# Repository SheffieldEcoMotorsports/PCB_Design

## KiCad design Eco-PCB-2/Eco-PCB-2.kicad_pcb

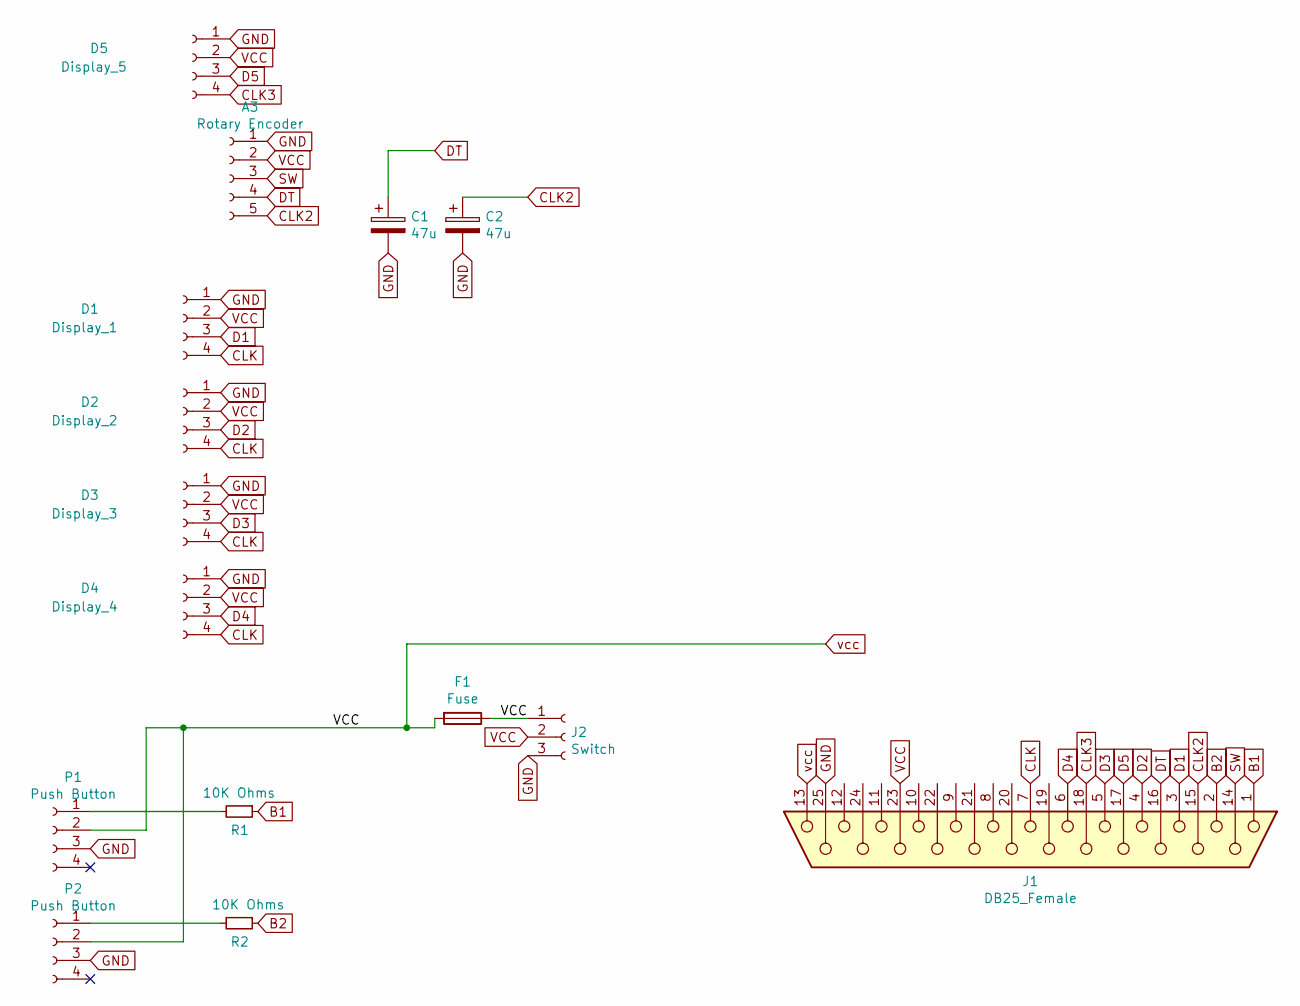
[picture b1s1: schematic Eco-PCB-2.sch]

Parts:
A3: Rotary Encoder; Rotary_Encoder_holes
C1, C2: 47u; C_Radial_D5.0mm_H11.0mm_P2.00mm
D1: Display_1; TM1637-Display-holes
D2: Display_2; TM1637-Display-holes
D3: Display_3; TM1637-Display-holes
D4: Display_4; TM1637-Display-holes
D5: Display_5; TM1637-Display-holes
F1: Fuse; Fuse-Holder
J1: DB25_Female; DSUB-25_Female_Vertical_P2.77x2.84mm_MountingHoles
J2: Switch; Red-Switch
P1, P2: Push Button; BUTTON
R1, R2: 10K Ohms; R_Axial_DIN0207_L6.3mm_D2.5mm_P10.16mm_Horizontal

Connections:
B1: J1.1, R1.1
B2: J1.2, R2.1
CLK: D1.4, D2.4, D3.4, D4.4, J1.7
CLK2: A3.5, C2.1, J1.15
CLK3: D5.4, J1.18
D1: D1.3, J1.3
D2: D2.3, J1.4
D3: D3.3, J1.5
D4: D4.3, J1.6
D5: D5.3, J1.17
DT: A3.4, C1.1, J1.16
GND: A3.1, C1.2, C2.2, D1.1, D2.1, D3.1, D4.1, D5.1, J1.25, J2.3, P1.3, P2.3
unnamed: P1.1, R1.2
unnamed: P2.1, R2.2
SW: A3.3, J1.14
VCC: A3.2, D1.2, D2.2, D3.2, D4.2, D5.2, F1.1, F1.2, J1.13, J1.23, J2.1, J2.2, P1.2, P2.2

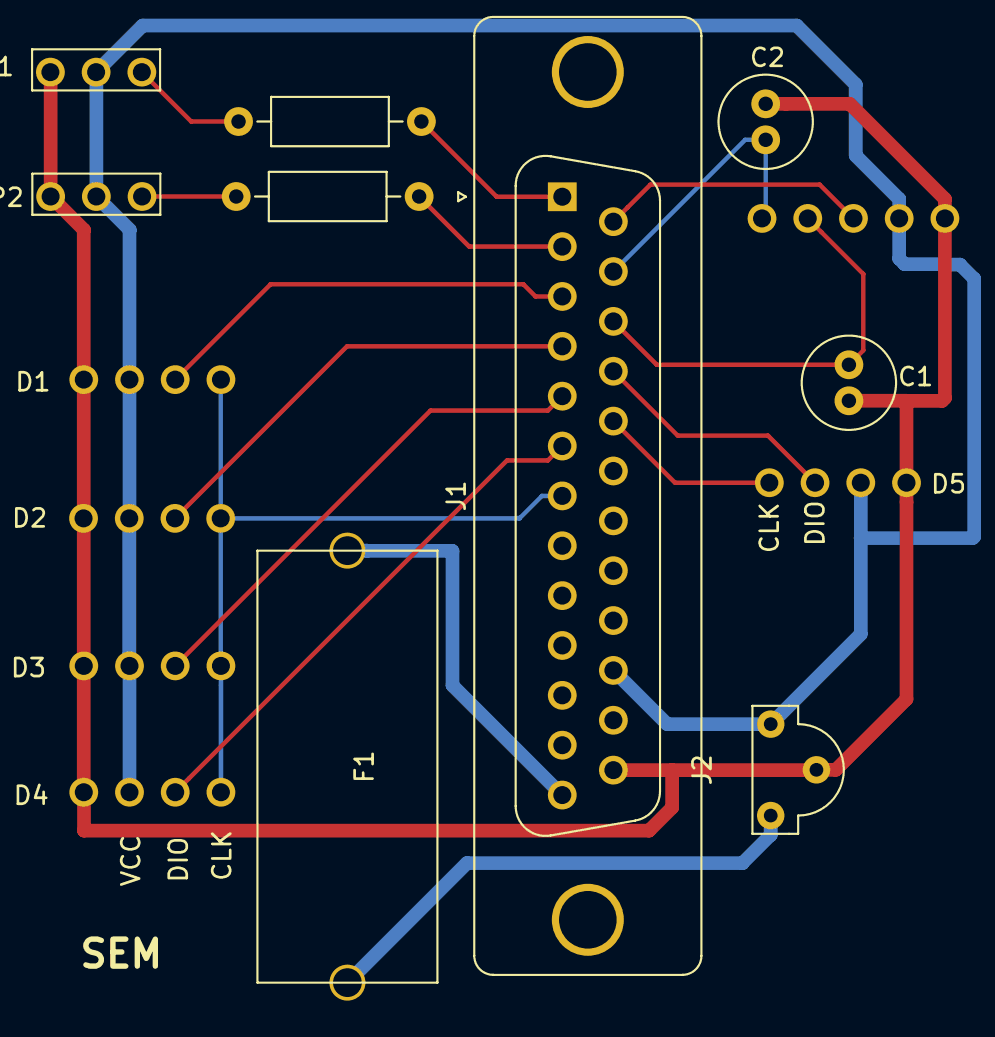
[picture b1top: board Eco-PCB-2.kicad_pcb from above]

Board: 2 copper layers, 15 parts (0 on the bottom side), 16 nets.

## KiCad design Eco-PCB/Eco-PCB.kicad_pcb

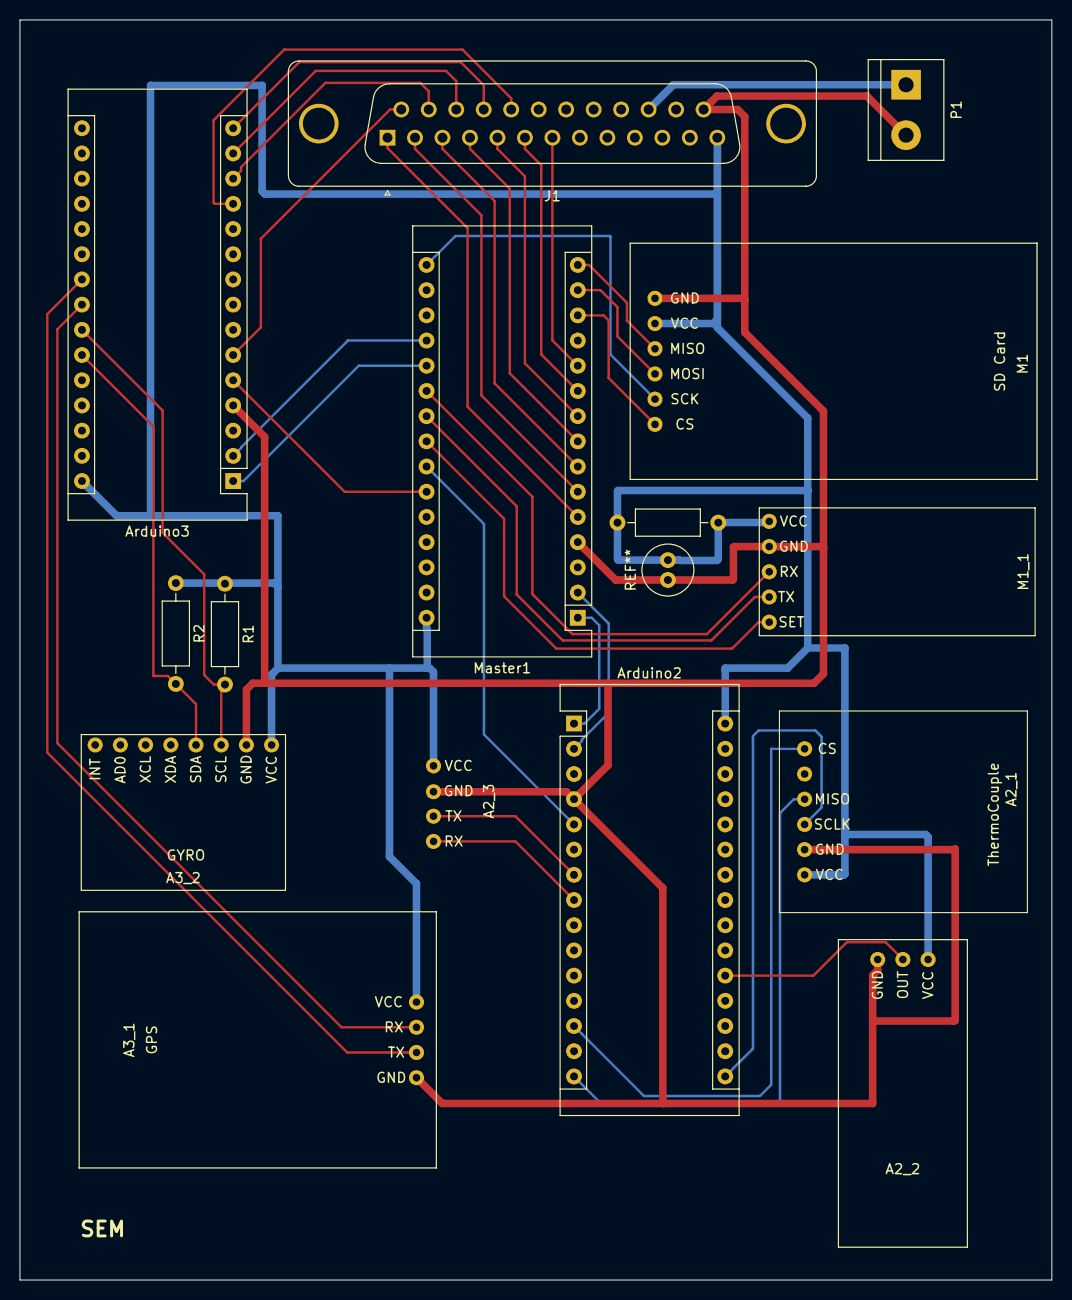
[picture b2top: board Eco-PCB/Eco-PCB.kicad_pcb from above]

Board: 2 copper layers, 104.0 x 127.0 mm, 15 parts (0 on the bottom side), 38 nets.

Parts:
A2_1: ThermoCouple; PMOD_TC1_Thermocouple
A2_2: Current Sensor; Current-Sensor
A2_3: BMS Serial Pins; BMS_Serial_Pins
A3_1: GPS
A3_2: GYRO; Gyro-MPU-6050
Arduino2, Arduino3: Arduino_Nano
J1: DB25_Female; DSUB-25_Female_Vertical_P2.77x2.84mm_MountingHoles
M1: SD Card; SD-CARD
M1_1: XSOURCE Wireless; XCSOURCE-Wireless
Master1: Arduino_Nano
P1: Power_Block; TerminalBlock_bornier-2_P5.08mm
R1, R1#2, R2: 10K Ohms; R_Axial_DIN0207_L6.3mm_D2.5mm_P10.16mm_Horizontal

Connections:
/CS: A2_1.1, Arduino2.13
/CS_: M1.6, Master1.13
/GND: A2_1.5, A2_2.3, A2_3.2, A3_1.1, A3_2.2, Arduino2.4, Arduino3.4, J1.25, M1.1, M1_1.2, Master1.4, P1.2
/MISO: A2_1.3, Arduino2.15
/MISO_: M1.3, Master1.15
/MOSI: M1.4, Master1.14
/OUT: A2_2.2, Arduino2.20
/RX: A2_3.4, Arduino2.8
/RX_: M1_1.3, Master1.21
/RX_3: A3_1.3, Arduino3.23
/SCK: M1.5, Master1.16
/SCL: A3_2.4, Arduino3.25, R2.2
/SCLK: A2_1.4, Arduino2.16
/SDA: A3_2.3, Arduino3.24, R1#2.2
/SET: M1_1.5, Master1.23
/TX: A2_3.3, Arduino2.7
/TX_: M1_1.4, Master1.22
/TX_3: A3_1.2, Arduino3.22
/VCC_1: J1.23, P1.1
CLK2: Arduino3.13, J1.15
CLK3: Arduino3.12, J1.18
D5: Arduino3.15, J1.17
DT: Arduino3.14, J1.16
unnamed: Arduino2.1, Master1.1
unnamed: Arduino2.2, Master1.2
unnamed: Arduino3.1, Master1.20
unnamed: Arduino3.2, Master1.19
unnamed: J1.1, Master1.5
unnamed: J1.2, Master1.6
unnamed: J1.3, Master1.7
unnamed: J1.4, Master1.8
unnamed: J1.5, Master1.9
unnamed: J1.6, Master1.10
unnamed: J1.7, Master1.11
SW: Arduino3.6, J1.14
VCC: A2_1.6, A2_2.1, A2_3.1, A3_1.4, A3_2.1, Arduino2.30, Arduino3.30, J1.13, M1.2, M1_1.1, Master1.30, R1.1, R1.2, R1#2.1, R2.1
int: Arduino2.5, Master1.24
int2: Arduino3.5, Master1.25

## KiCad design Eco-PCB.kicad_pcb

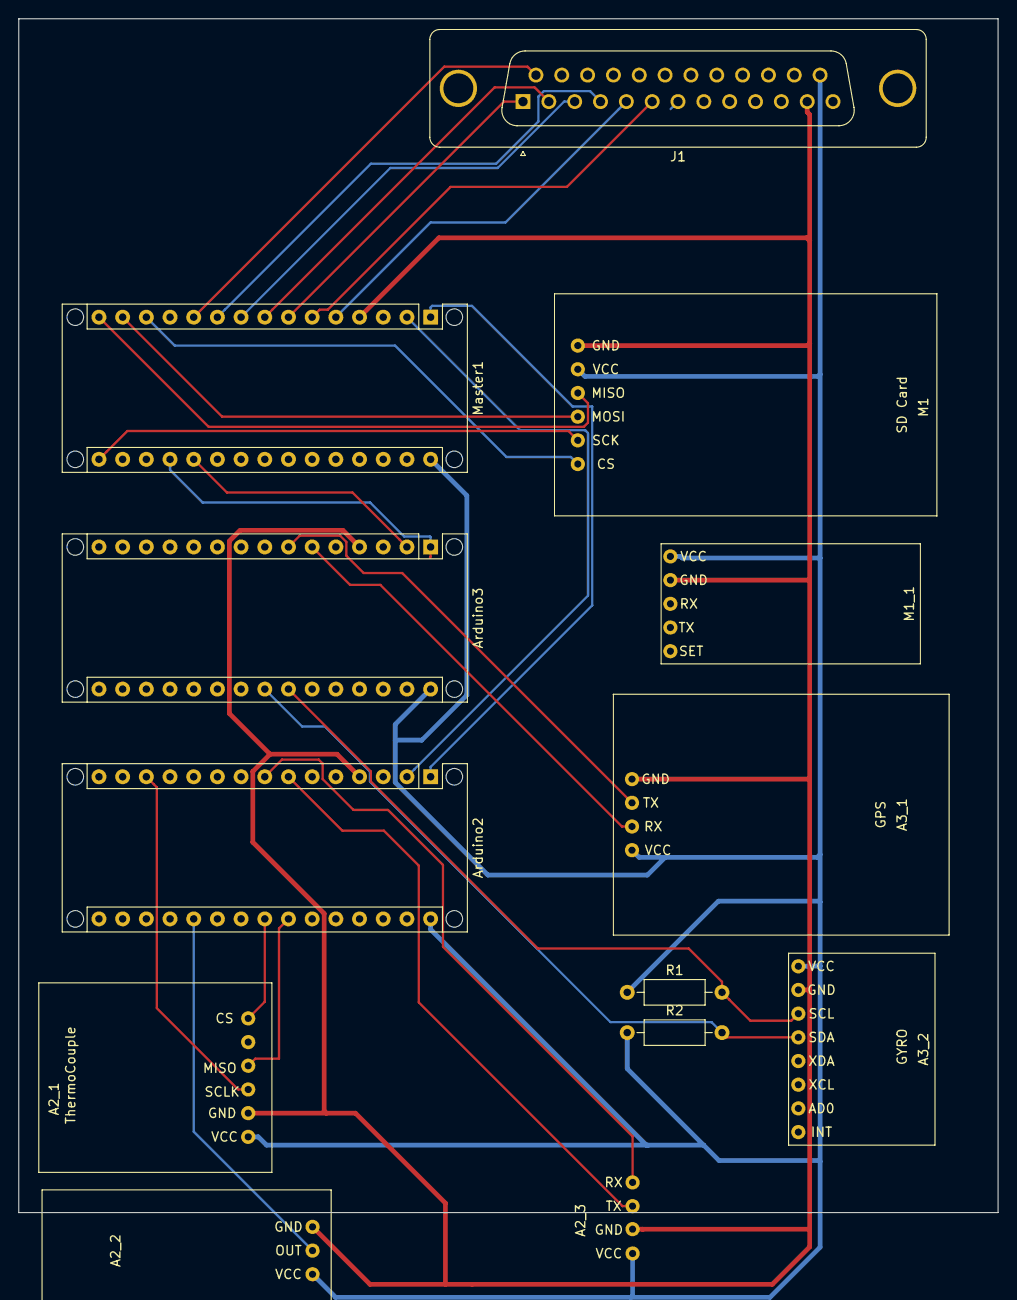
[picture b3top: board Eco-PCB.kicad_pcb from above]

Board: 2 copper layers, 105.0 x 128.0 mm, 13 parts (0 on the bottom side), 27 nets.

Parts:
A2_1: ThermoCouple; PMOD_TC1_Thermocouple
A2_2: Current Sensor; Current-Sensor
A2_3: BMS Serial Pins; BMS_Serial_Pins
A3_1: GPS
A3_2: GYRO; Gyro-MPU-6050
Arduino2, Arduino3: Arduino_Nano; Arduino_Nano_WithMountingHoles
J1: DB25_Female; DSUB-25_Female_Vertical_P2.77x2.84mm_MountingHoles
M1: SD Card; SD-CARD
M1_1: XSOURCE Wireless; XCSOURCE-Wireless
Master1: Arduino_Nano; Arduino_Nano_WithMountingHoles
R1, R2: 10K Ohms; R_Axial_DIN0207_L6.3mm_D2.5mm_P10.16mm_Horizontal

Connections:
/3.3V: A2_1.1, A2_2.1, A2_3.1, A3_1.4, A3_2.1, Arduino2.30, Arduino3.30, J1.25, M1.2, M1_1.1, Master1.30, R1.1, R2.1
/CS: A2_1.6, Arduino2.23
/CS_: M1.6, Master1.13
/MISO: A2_1.4, Arduino2.24
/MISO_: M1.3, Master1.15
/MOSI: M1.4, Master1.14
/OUT: A2_2.2, Arduino2.20
/RX: A2_3.4, Arduino2.8
/RX_3: A3_1.3, Arduino3.6
/SCK: M1.5, Master1.16
/SCL: A3_2.4, Arduino3.23, R2.2
/SCLK: A2_1.3, Arduino2.13
/SDA: A3_2.3, Arduino3.24, R1.2
/TX: A2_3.3, Arduino2.7
/TX_3: A3_1.2, Arduino3.7
GND: A2_1.2, A2_2.3, A2_3.2, A3_1.1, A3_2.2, Arduino2.4, Arduino3.4, J1.12, M1.1, M1_1.2, Master1.4
unnamed: Arduino2.1, Master1.1
unnamed: Arduino2.2, Master1.2
unnamed: Arduino3.1, Master1.19
unnamed: Arduino3.2, Master1.20
unnamed: J1.1, Master1.7
unnamed: J1.2, Master1.8
unnamed: J1.3, Master1.9
unnamed: J1.4, Master1.10
unnamed: J1.5, Master1.5
unnamed: J1.6, Master1.6
unnamed: J1.14, Master1.11

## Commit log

2019-05-30 Initial Commit of files
2019-05-30 Removed unnecessary files and only kept the updated ones
2019-05-30 New PCB 1 Design with correct width for VCC & GND
2019-05-31 Pcb 1 design done V1.0
2019-06-06 PCB1 added CLK line & PCB2 Design done
2019-06-06 PCB2 Print Files Added
2019-06-13 updated pin sizes issue and spacing on PCB2
